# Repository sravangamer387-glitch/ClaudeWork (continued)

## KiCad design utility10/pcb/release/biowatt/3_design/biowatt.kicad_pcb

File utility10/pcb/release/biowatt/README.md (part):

# BioWatt MFC energy harvester (BQ25570) (rev A)

BioWatt microbial-fuel-cell energy harvester (44 x 40 mm): TI BQ25570 boost charger with MPPT, buck output, VBAT_OK, megohm setting dividers; one protected Li-ion cell as storage.

**Status: engineering release, software-verified only (ERC on the netlist, KiCad DRC, netlist cross-check, SPICE where noted). Not yet built, not reviewed by a second engineer, not certified.**

## Specification
- Board 44 x 40 mm, 2 layers, 1.6 mm FR-4, 1 oz copper, rounded corners R2.0 mm, 2 x M2.5 mounting holes, 2 fiducials.
- Rules used: min track 0.2 mm (power 0.4 mm), min clearance 0.15 mm, via 0.6/0.3 mm, GND pour on both layers, 30 stitching vias.
- Finish: ENIG recommended (HASL lead-free acceptable); green mask, white silk; IPC class 2.
- 29 parts, 20 nets.

## Circuit description
- **Harvester:** BQ25570 (SLUSBH2G). VIN_DC from the fuel cell through L1 = 22 uH, CIN 4.7 uF; VOC_SAMP tied to GND = MPPT at 50 % of Voc (the maximum-power point of a source with a linear polarisation curve); VREF_SAMP 10 nF; EN tied to GND (enabled); VOUT_EN tied to VSTOR; NC pins tied to the PowerPAD.
- **Settings (equations from the datasheet, VBIAS 1.21 V):** VBAT_OV 3.95 V (ROV1 5.6 M, ROV2 5.6 M + 1 M); VBAT_OK 3.35 V falling and 3.63 V rising (ROK1 4.3 M, ROK2 5.6 M + 1 M + 1 M, ROK3 1 M); VOUT 3.35 V (ROUT1 4.3 M, ROUT2 5.6 M + 1 M + 1 M). Dividers go from VRDIV to GND.
- **Output:** buck L2 = 10 uH, COUT 22 uF; header with VOUT, GND and the VBAT_OK flag for the sensor tag. Storage: a protected single Li-ion/LiPo cell on VBAT (22 uF) with CSTOR 4.7 uF + CBYP 0.1 uF at VSTOR.

## Power
Harvester quiescent about 0.5 uA (datasheet); output limited by what the fuel cell delivers (see biowatt/docs/budget.md).

## Verification
| Check | Result |
|---|---|
| Electrical rule check on the netlist (own ERC: unconnected pins, single-pin nets, output conflicts, unpowered supplies, symbol/footprint pin match) | 0 errors, 0 warnings |
| KiCad DRC | 0 errors, 0 warnings; unconnected pads: 0 |
| Schematic netlist equals PCB netlist | yes |
| Router failures | 0 |
| 3D STEP export | yes |
| Independent Gerber parse (gerbonara): layers parsed, outline size equals the design | 9 layers, outline [44.1, 40.1] mm, match |

Enclosure (prototype shell for 3D printing): outer 49.2 x 45.2 x 15.6 mm, collision/opening check: pass

## Bill of materials
| Ref | Value | Footprint | Manufacturer part | LCSC # | LCSC status |
|---|---|---|---|---|---|
| U1 | BQ25570RGRR | QFN-20-1EP_3.5x3.5mm_P0.5mm_EP2x2mm | BQ25570RGRR | C506250 | verified |
| J1 | MFC in (+ / -) | JST_PH_B2B-PH-K_1x02_P2.00mm_Vertical | JST B2B-PH-K-S | C131337 | verified |
| J2 | Storage cell (+ / -), protected | JST_PH_B2B-PH-K_1x02_P2.00mm_Vertical | JST B2B-PH-K-S | C131337 | verified |
| J3 | Tag out (VOUT, GND, VBAT_OK) | JST_PH_B3B-PH-K_1x03_P2.00mm_Vertical | JST B3B-PH-K-S | C131339 | verified |
| L1 | 22u | L_Coilcraft_LPS4018 | Coilcraft LPS4018-223MRC | C5278935 | verified |
| L2 | 10u | L_Changjiang_FNR3015S | ZE ZENR3015T100M | C42427989 | verified |
| C1 | 4.7u | C_0603_1608Metric | Samsung CL10A475KP8NNNC X5R 10V | C1705 | verified |
| C2 | 100n | C_0603_1608Metric | Samsung CL10B104KB8NNNC 0603 100nF X7R 50V | C1591 | verified |
| C3 | 4.7u | C_0603_1608Metric | Samsung CL10A475KP8NNNC X5R 10V | C1705 | verified |
| C4 | 22u/10V | C_0805_2012Metric | Samsung CL21A226MPQNNNE | C29277 | verified |
| C5 | 22u/10V | C_0805_2012Metric | Samsung CL21A226MPQNNNE | C29277 | verified |
| C6 | 10n | C_0603_1608Metric | Samsung CL10B103KB8NNNC 0603 10nF X7R 50V | C1589 | verified |
| R3 | 5.6M | R_0603_1608Metric | FOJAN FRC0603F5604TS | C2933237 | verified |
| R2 | 1M | R_0603_1608Metric | UNI-ROYAL 0603WAF1004T5E | C22935 | verified |
| R1 | 5.6M | R_0603_1608Metric | FOJAN FRC0603F5604TS | C2933237 | verified |
| R4 | 4.3M | R_0603_1608Metric | FH RS-03L4304FT | C136595 | verified |
| R5 | 5.6M | R_0603_1608Metric | FOJAN FRC0603F5604TS | C2933237 | verified |
| R6 | 1M | R_0603_1608Metric | UNI-ROYAL 0603WAF1004T5E | C22935 | verified |
| R7 | 1M | R_0603_1608Metric | UNI-ROYAL 0603WAF1004T5E | C22935 | verified |
| R8 | 1M | R_0603_1608Metric | UNI-ROYAL 0603WAF1004T5E | C22935 | verified |
| R9 | 1M | R_0603_1608Metric | UNI-ROYAL 0603WAF1004T5E | C22935 | verified |
| R10 | 4.3M | R_0603_1608Metric | FH RS-03L4304FT | C136595 | verified |
| R11 | 5.6M | R_0603_1608Metric | FOJAN FRC0603F5604TS | C2933237 | verified |
| R12 | 1M | R_0603_1608Metric | UNI-ROYAL 0603WAF1004T5E | C22935 | verified |
| R13 | 1M | R_0603_1608Metric | UNI-ROYAL 0603WAF1004T5E | C22935 | verified |
| TP1 | TP | TestPoint_Pad_D1.5mm |  |  |  |
| TP2 | TP | TestPoint_Pad_D1.5mm |  |  |  |
| TP3 | TP | TestPoint_Pad_D1.5mm |  |  |  |
| TP4 | TP | TestPoint_Pad_D1.5mm |  |  |  |

`verified` = LCSC number confirmed by web search on 2026-10-31/11-01; `memory` = from my recollection, **check on lcsc.com before ordering**; empty = no number chosen (through-hole connectors, switches, buzzer, test points: hand-assembled or chosen by the buyer). `*_JLC_BOM.csv` / `*_JLC_CPL.csv` list only the parts with an LCSC number; JLCPCB rotation corrections (CPL) must be checked in their viewer.

## Assembly notes
- Reflow (JLCPCB SMT): all SMD parts with an LCSC number. Hand-solder: JST connectors, pin headers, buzzer, switches, test points as listed in the BOM. Fiducials and mounting holes are in the Gerbers.
- Polarity: LED cathode toward GND (silk marks), electrolytic none, diode D2 cathode to +V, Q2 orientation as footprint (SOT-23 pin 1 = gate).
- Programming: ISP header J2 (pin 1 = MISO, square pad). Flash the matching image from `utility10/firmware/release/`: Seeti Counter `4MHz/seeti_prod.hex` (production firmware: timer-triggered 16 kS/s ADC, scan mode to find the real whistle frequency, battery check), Rain Alert `8MHz/rain_alert.hex`, Bijli Meter Reader `8MHz/bijli_meter.hex` (demo-grade firmware, to be hardened).

## Bring-up and test
1. With no cell and no source: nothing to measure; check no shorts VSTOR-GND, VOUT-GND.
2. Fit the protected cell: VSTOR follows the cell, VBAT_OK goes high above about 3.63 V.
3. Feed 0.6-1.0 V from a bench supply through 1 kohm: VSTOR rises (cold start needs VIN of at least 0.6 V).
4. Connect the fuel cell, measure VIN_DC under load: it should settle near half of the open-circuit voltage.
5. Measure VOUT = 3.35 V +-3 %.

## Files
`1_fabrication/` Gerber + drill zip (upload to JLCPCB/any fab), fab notes, copper plot
`2_assembly/` JLC BOM + CPL (SMD parts JLC assembles), full BOM with LCSC numbers for every part, pick-and-place, assembly drawing
`3_design/` KiCad 7 project (pcb, schematic, libs), netlist, STEP model, schematic PDF, renders
`4_enclosure/` printable base and lid STL
`5_verification/` DRC, ERC, verification and readiness reports

## Known limits and review checklist
- Layout was produced by a custom router and software placement; a human layout review (analog routing, ground returns, creepage, connector mechanics, silkscreen) is still required.
- Not verified: EMC, ESD (apart from TVS parts where fitted), thermal, real component tolerances, supplier stock/price, assembly house design-for-manufacture check (run JLCPCB's DFM check on the Gerbers).
- Firmware thresholds are placeholders to be calibrated on prototypes.

## Manufacturing readiness (automatic check)

| Check | Result |
|---|---|
| gerber layers and drill present | PASS |
| drc errors 0 | PASS |
| unconnected 0 | PASS |
| netlist matches schematic | PASS |
| erc errors 0 | PASS |
| independent gerber check clean | PASS |
| every part has lcsc number | PASS |
| every lcsc number verified | PASS |
| cpl rows equal jlc bom parts | PASS |
| step model | PASS |
| KiCad DRC warnings | 0 |
| **Order ready** | **YES** |

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
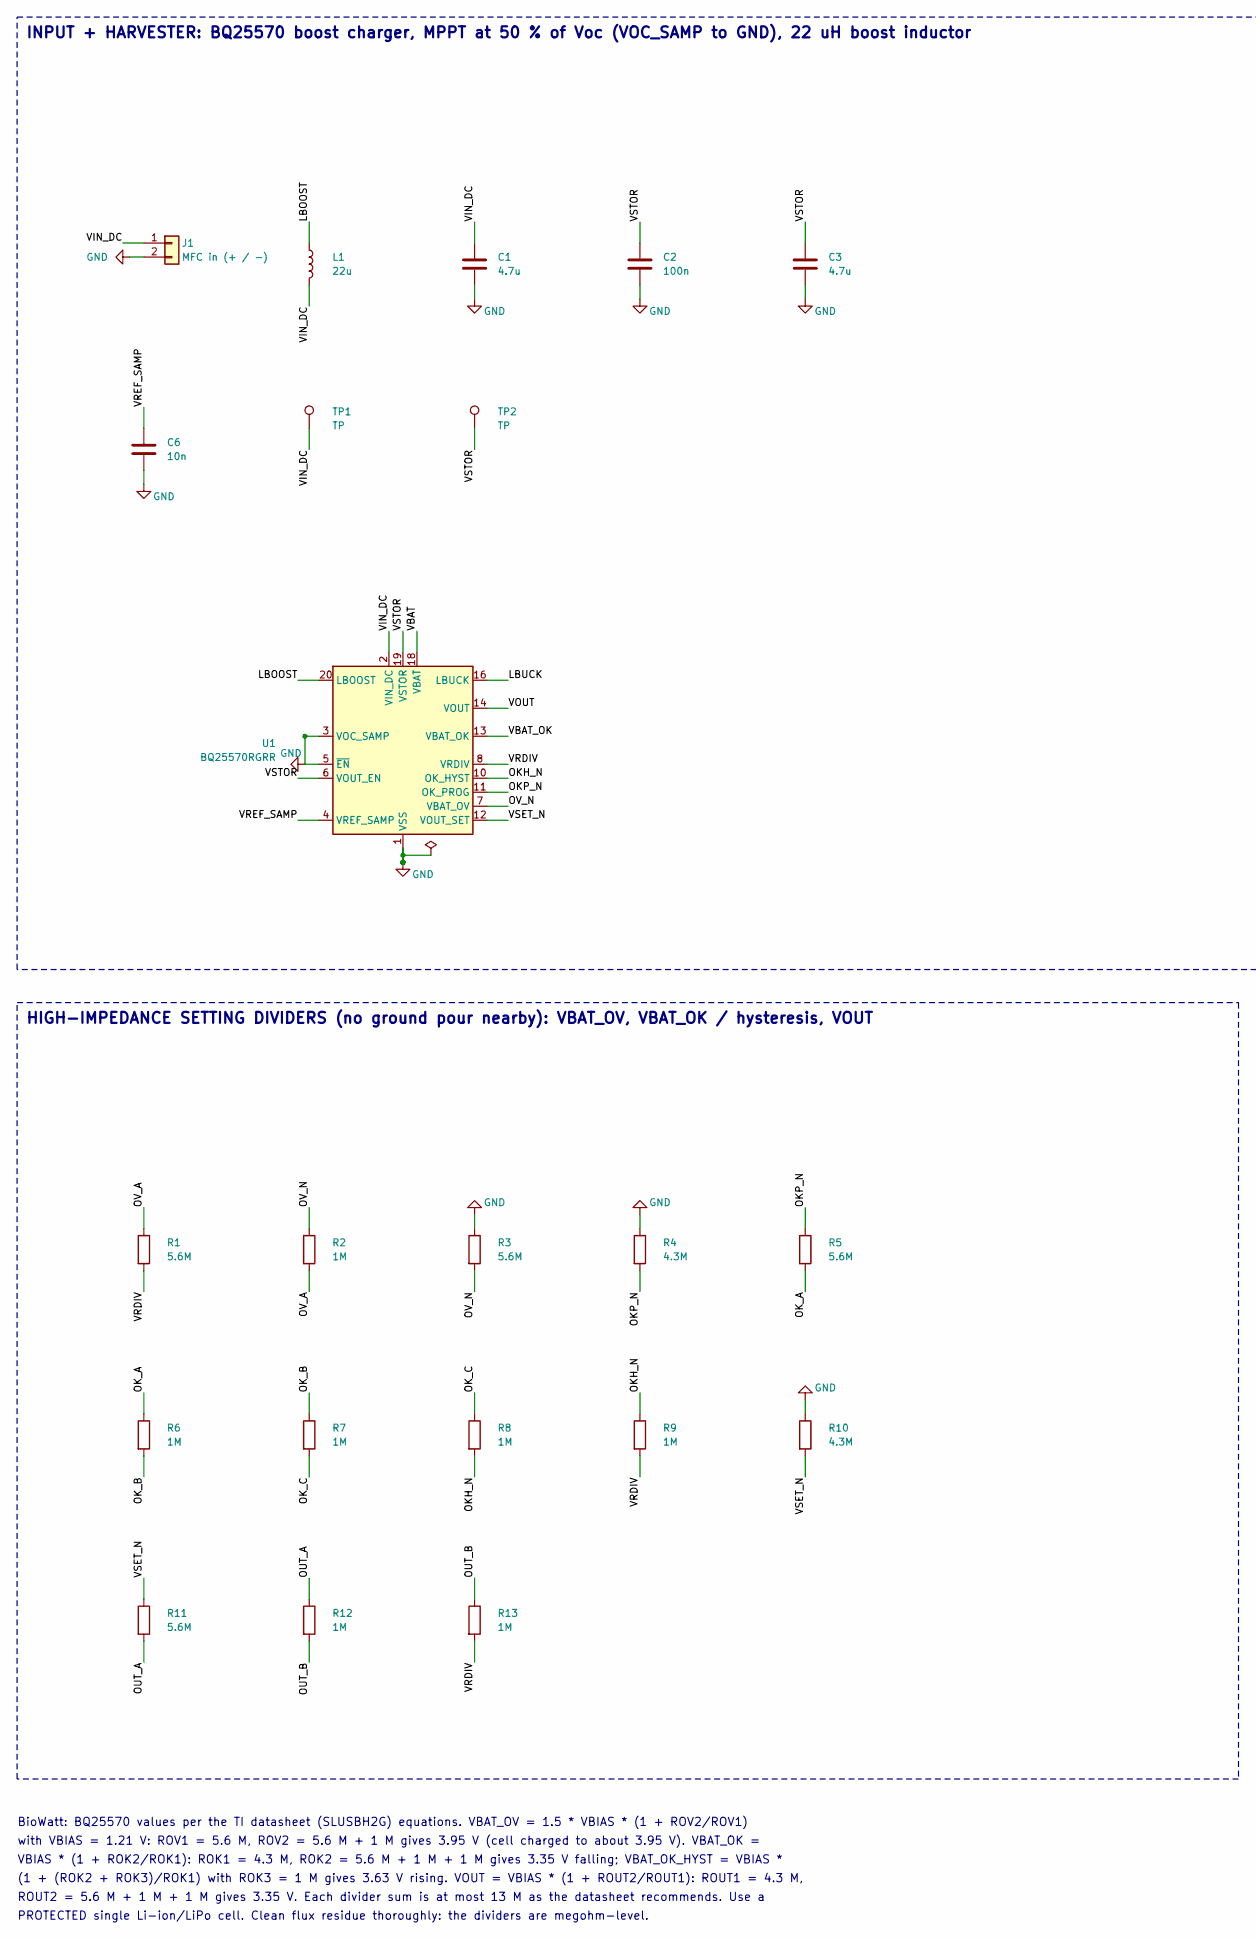
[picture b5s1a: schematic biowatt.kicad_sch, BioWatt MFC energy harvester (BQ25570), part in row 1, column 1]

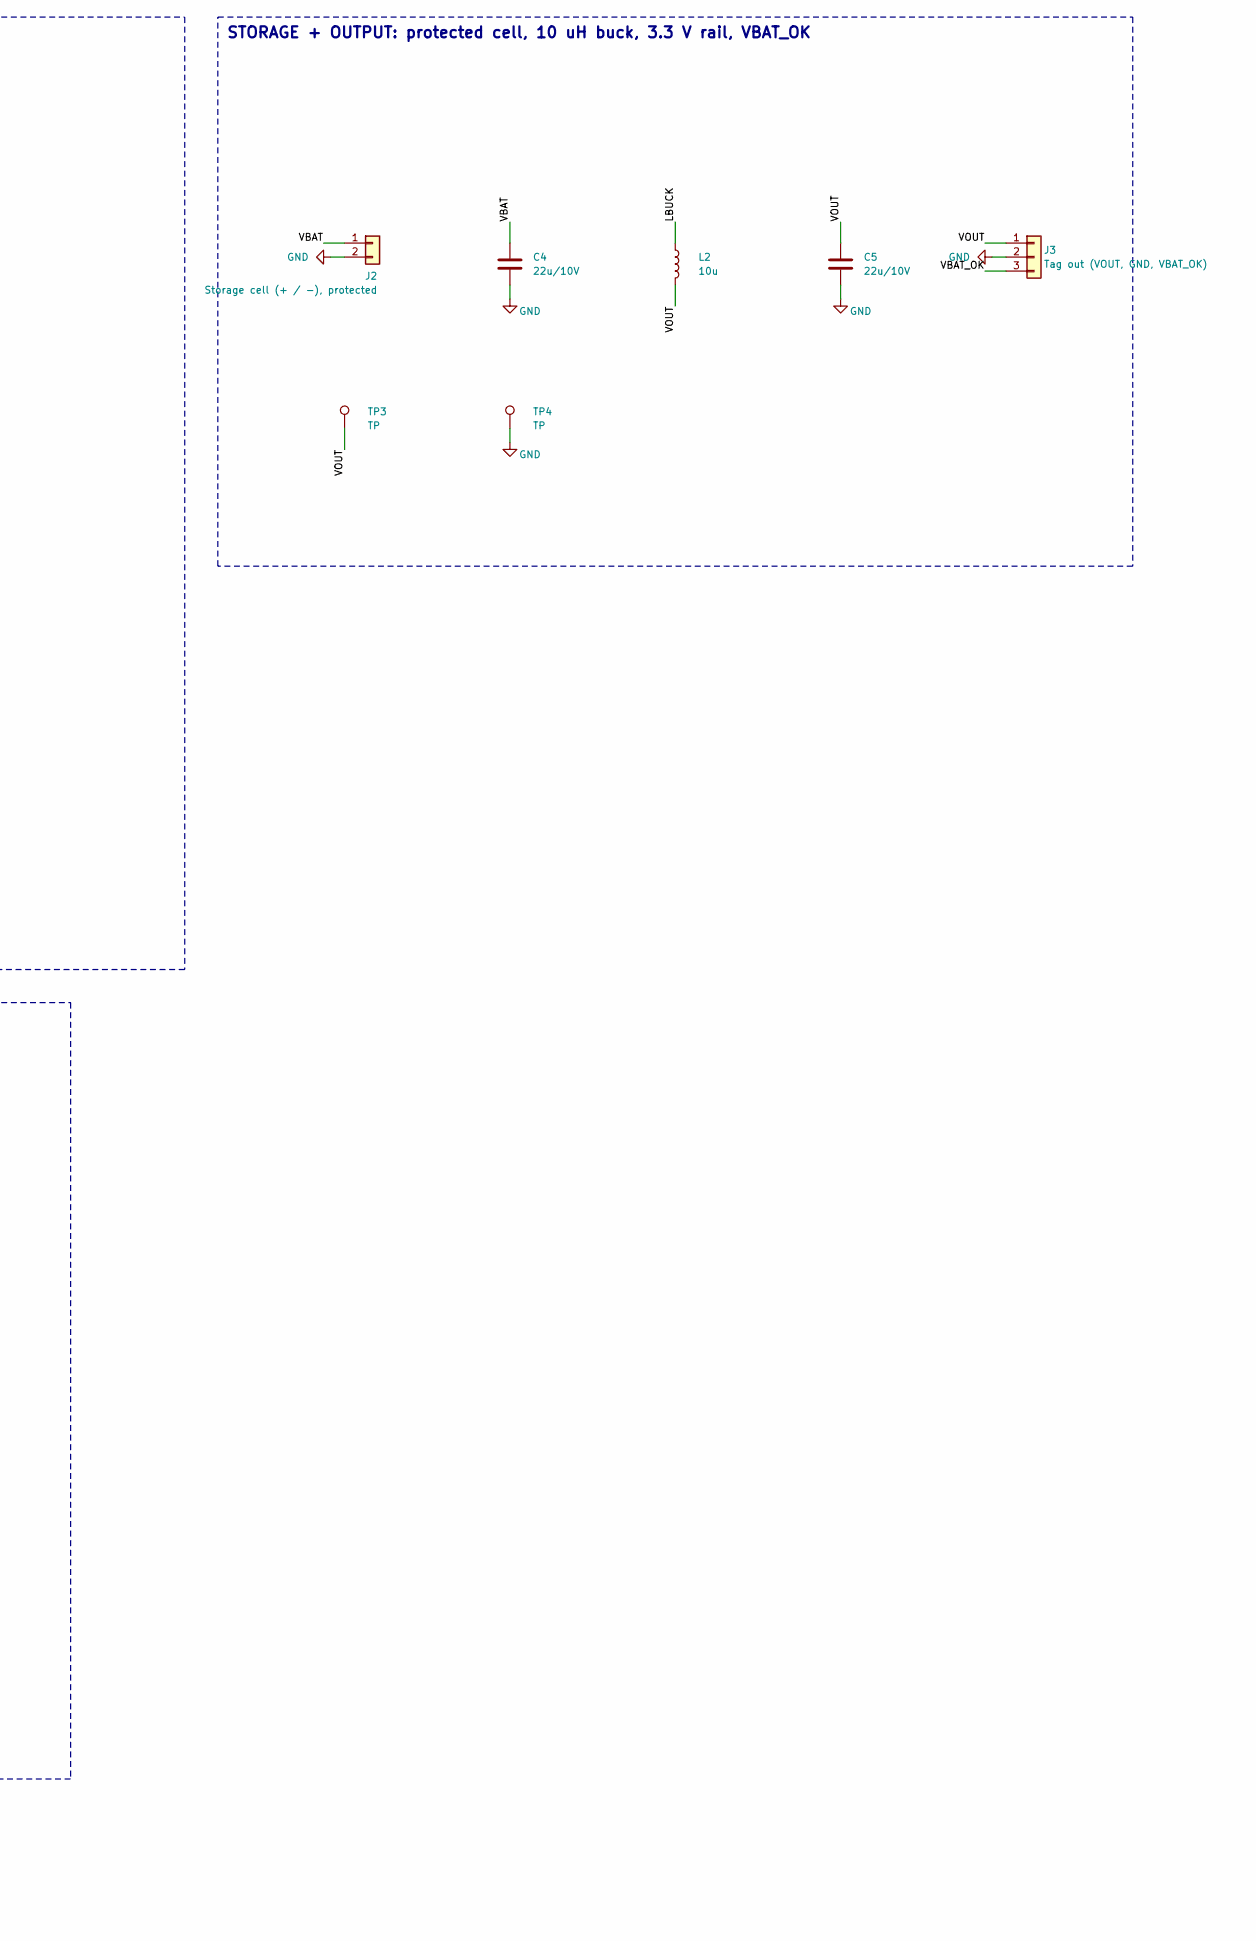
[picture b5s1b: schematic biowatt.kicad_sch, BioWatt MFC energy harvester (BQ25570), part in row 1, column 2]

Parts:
C1, C3: 4.7u; C_0603_1608Metric
C2: 100n; C_0603_1608Metric
C4, C5: 22u/10V; C_0805_2012Metric
C6: 10n; C_0603_1608Metric
J1: MFC in (+ / -); JST_PH_B2B-PH-K_1x02_P2.00mm_Vertical
J2: Storage cell (+ / -), protected; JST_PH_B2B-PH-K_1x02_P2.00mm_Vertical
J3: Tag out (VOUT, GND, VBAT_OK); JST_PH_B3B-PH-K_1x03_P2.00mm_Vertical
L1: 22u; L_Coilcraft_LPS4018
L2: 10u; L_Changjiang_FNR3015S
R1, R3, R5, R11: 5.6M; R_0603_1608Metric
R2, R6, R7, R8, R9, R12, R13: 1M; R_0603_1608Metric
R4, R10: 4.3M; R_0603_1608Metric
TP1, TP2, TP3, TP4: TP; TestPoint_Pad_D1.5mm
U1: BQ25570RGRR; QFN-20-1EP_3.5x3.5mm_P0.5mm_EP2x2mm

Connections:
GND: C1.2, C2.2, C3.2, C4.2, C5.2, C6.2, J1.2, J2.2, J3.2, R3.1, R4.1, R10.1, TP4.1, U1.1 (VSS), U1.3 (VOC_SAMP), U1.5 (~EN), U1.9 (VSS), U1.15 (VSS), U1.17 (VSS), U1.21 (VSS)
LBOOST: L1.1, U1.20 (LBOOST)
LBUCK: L2.1, U1.16 (LBUCK)
OKH_N: R8.2, R9.1, U1.10 (OK_HYST)
OKP_N: R4.2, R5.1, U1.11 (OK_PROG)
OK_A: R5.2, R6.1
OK_B: R6.2, R7.1
OK_C: R7.2, R8.1
OUT_A: R11.2, R12.1
OUT_B: R12.2, R13.1
OV_A: R1.1, R2.2
OV_N: R2.1, R3.2, U1.7 (VBAT_OV)
VBAT: C4.1, J2.1, U1.18 (VBAT)
VBAT_OK: J3.3, U1.13 (VBAT_OK)
VIN_DC: C1.1, J1.1, L1.2, TP1.1, U1.2 (VIN_DC)
VOUT: C5.1, J3.1, L2.2, TP3.1, U1.14 (VOUT)
VRDIV: R1.2, R9.2, R13.2, U1.8 (VRDIV)
VREF_SAMP: C6.1, U1.4 (VREF_SAMP)
VSET_N: R10.2, R11.1, U1.12 (VOUT_SET)
VSTOR: C2.1, C3.1, TP2.1, U1.6 (VOUT_EN), U1.19 (VSTOR)

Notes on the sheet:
INPUT + HARVESTER: BQ25570 boost charger, MPPT at 50 % of Voc (VOC_SAMP to GND), 22 uH boost inductor
STORAGE + OUTPUT: protected cell, 10 uH buck, 3.3 V rail, VBAT_OK
HIGH-IMPEDANCE SETTING DIVIDERS (no ground pour nearby): VBAT_OV, VBAT_OK / hysteresis, VOUT
BioWatt: BQ25570 values per the TI datasheet (SLUSBH2G) equations. VBAT_OV = 1.5 * VBIAS * (1 + ROV2/ROV1)
with VBIAS = 1.21 V: ROV1 = 5.6 M, ROV2 = 5.6 M + 1 M gives 3.95 V (cell charged to about 3.95 V). VBAT_OK =
VBIAS * (1 + ROK2/ROK1): ROK1 = 4.3 M, ROK2 = 5.6 M + 1 M + 1 M gives 3.35 V falling; VBAT_OK_HYST = VBIAS *
(1 + (ROK2 + ROK3)/ROK1) with ROK3 = 1 M gives 3.63 V rising. VOUT = VBIAS * (1 + ROUT2/ROUT1): ROUT1 = 4.3 M,
ROUT2 = 5.6 M + 1 M + 1 M gives 3.35 V. Each divider sum is at most 13 M as the datasheet recommends. Use a
PROTECTED single Li-ion/LiPo cell. Clean flux residue thoroughly: the dividers are megohm-level.

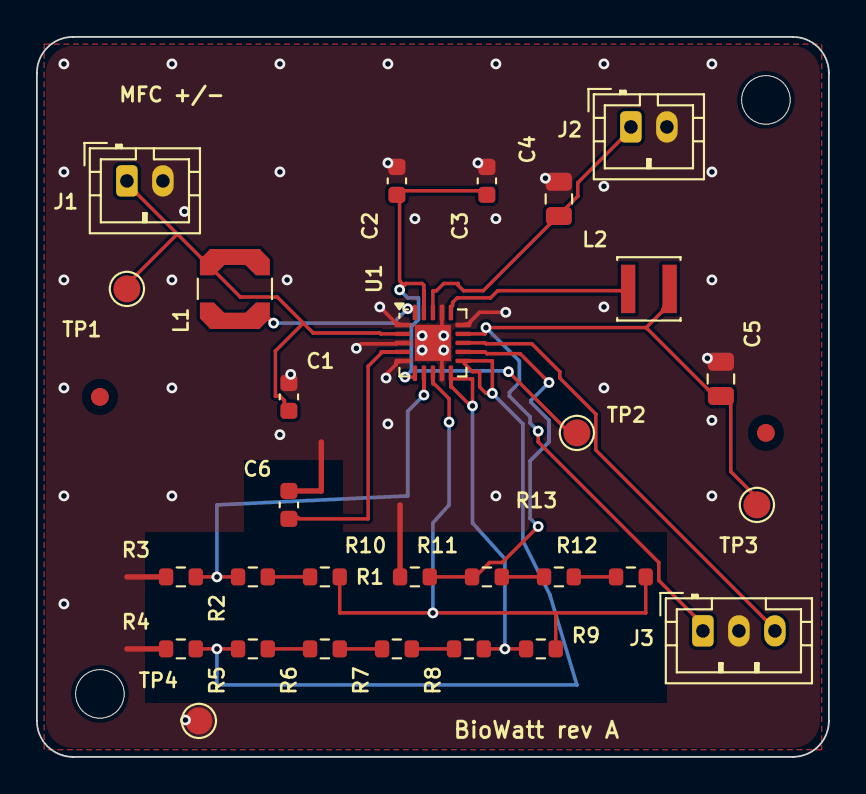
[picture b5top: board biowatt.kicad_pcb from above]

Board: 2 copper layers, 44.0 x 40.0 mm, 33 parts (0 on the bottom side), 20 nets.

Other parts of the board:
FID1, FID2: Fiducial; Fiducial_1mm_Mask2mm
H1, H2: M2.5; MountingHole_2.7mm_M2.5

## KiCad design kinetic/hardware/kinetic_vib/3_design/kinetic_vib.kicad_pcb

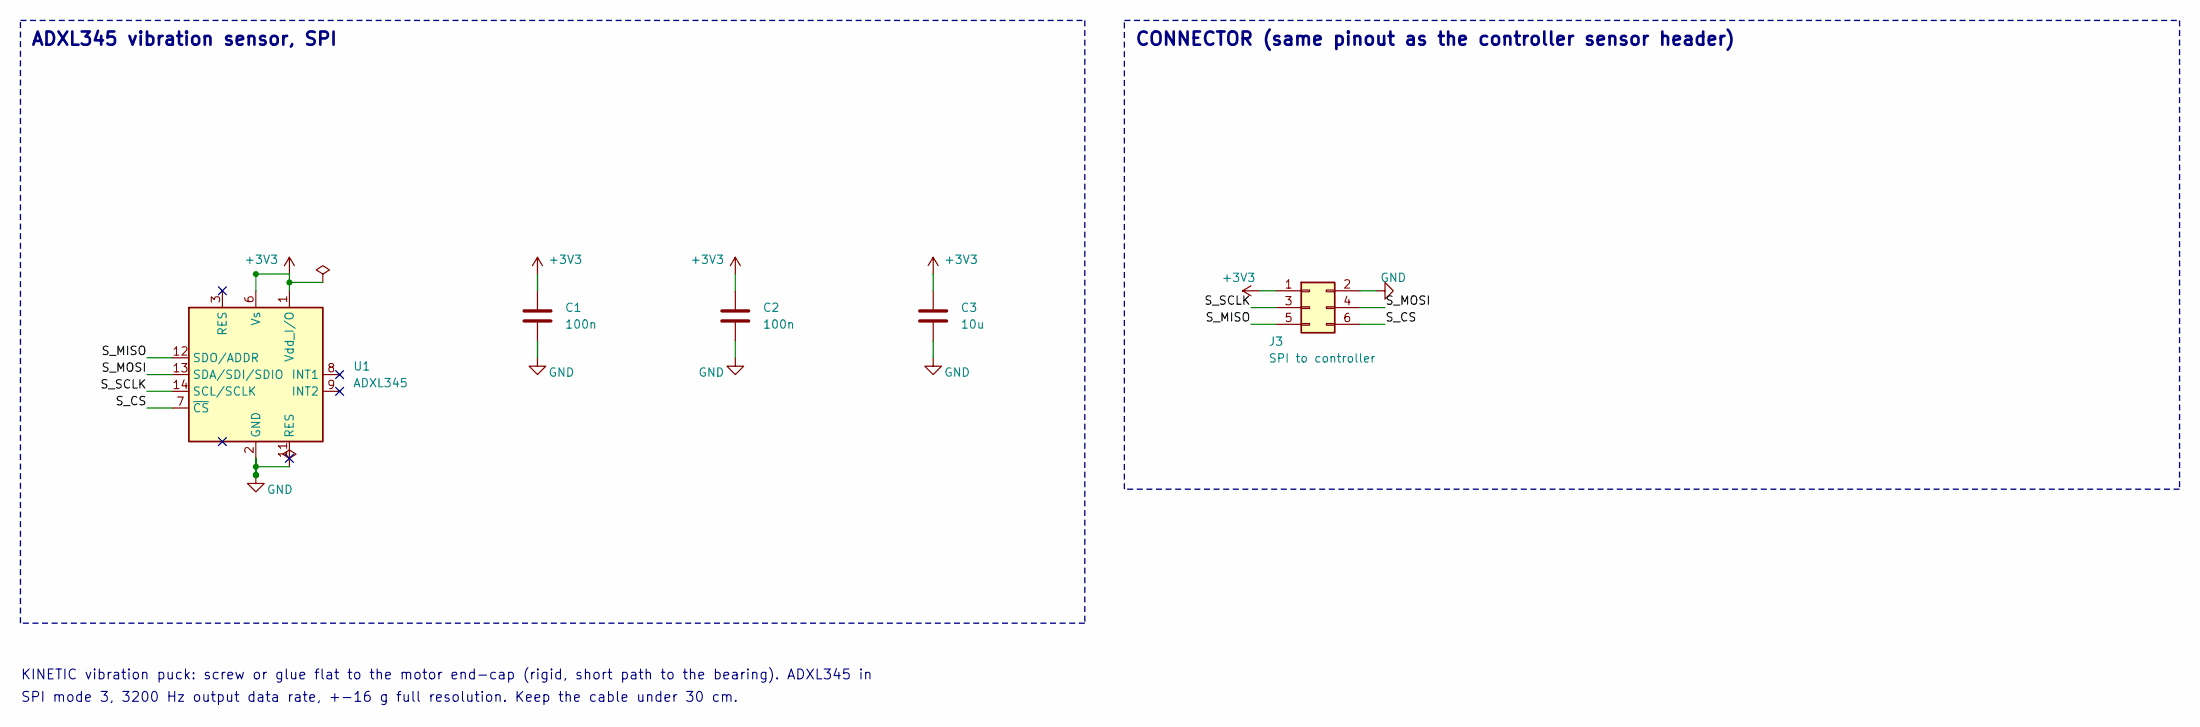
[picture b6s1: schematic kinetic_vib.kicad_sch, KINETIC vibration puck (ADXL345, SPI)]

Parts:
C1, C2: 100n; C_0603_1608Metric
C3: 10u; C_0805_2012Metric
J3: SPI to controller; PinHeader_2x03_P2.54mm_Vertical
U1: ADXL345; LGA-14_3x5mm_P0.8mm_LayoutBorder1x6y

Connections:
+3V3: C1.1, C2.1, C3.1, J3.1, U1.1 (Vdd_I/O), U1.6 (Vs)
GND: C1.2, C2.2, C3.2, J3.2, U1.2 (GND), U1.4 (GND), U1.5 (GND)
S_CS: J3.6, U1.7 (~CS)
S_MISO: J3.5, U1.12 (SDO/ADDR)
S_MOSI: J3.4, U1.13 (SDA/SDI/SDIO)
S_SCLK: J3.3, U1.14 (SCL/SCLK)

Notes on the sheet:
ADXL345 vibration sensor, SPI
CONNECTOR (same pinout as the controller sensor header)
KINETIC vibration puck: screw or glue flat to the motor end-cap (rigid, short path to the bearing). ADXL345 in
SPI mode 3, 3200 Hz output data rate, +-16 g full resolution. Keep the cable under 30 cm.

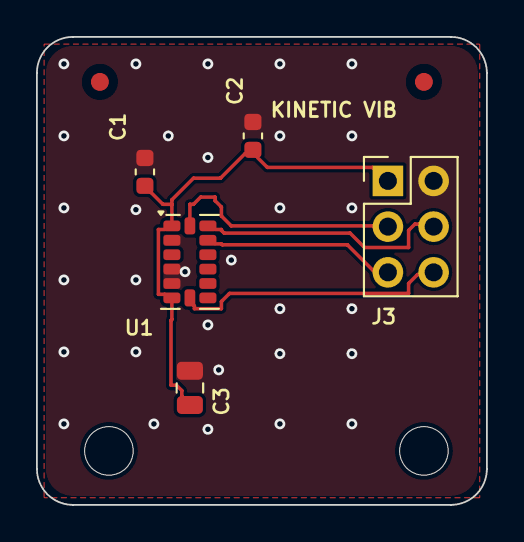
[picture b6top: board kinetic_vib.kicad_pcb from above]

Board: 2 copper layers, 25.0 x 26.0 mm, 9 parts (0 on the bottom side), 6 nets.

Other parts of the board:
FID1, FID2: Fiducial; Fiducial_1mm_Mask2mm
H1, H2: M2.5; MountingHole_2.7mm_M2.5

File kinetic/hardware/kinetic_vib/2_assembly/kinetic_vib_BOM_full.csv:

Ref,Value,Footprint,Manufacturer part,LCSC #,LCSC status,Assembly
U1,ADXL345,Package_LGA:LGA-14_3x5mm_P0.8mm_LayoutBorder1x6y,ADXL345BCCZ-RL7,C9667,verified,SMT (JLC)
C1,100n,Capacitor_SMD:C_0603_1608Metric,0603 100nF X7R,C14663,verified,SMT (JLC)
C2,100n,Capacitor_SMD:C_0603_1608Metric,0603 100nF X7R,C14663,verified,SMT (JLC)
C3,10u,Capacitor_SMD:C_0805_2012Metric,0805 10uF X5R,C15850,verified,SMT (JLC)
J3,SPI to controller,Connector_PinHeader_2.54mm:PinHeader_2x03_P2.54mm_Vertical,ZHOURI 2.54-2*3,C5116479,verified,hand/THT

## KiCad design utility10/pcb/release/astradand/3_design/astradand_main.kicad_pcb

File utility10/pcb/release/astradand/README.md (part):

# ASTRADAND gesture wand - main board (rev A)

ASTRADAND gesture wand main board (146 x 26 mm): ATmega328P at 8 MHz and 3.3 V, MPU-6050 6-axis IMU on I2C, six WS2812B-Mini pixels, differential piezo, haptic motor driver, trigger switch, 3xAAA power with reverse-polarity PMOS.

**Status: engineering release, software-verified only (ERC on the netlist, KiCad DRC, netlist cross-check, SPICE where noted). Not yet built, not reviewed by a second engineer, not certified.**

## Specification
- Board 146 x 26 mm, 2 layers, 1.6 mm FR-4, 1 oz copper, rounded corners R2.5 mm, 2 x M2.5 mounting holes, 2 fiducials.
- Rules used: min track 0.2 mm (power 0.4 mm), min clearance 0.15 mm, via 0.6/0.3 mm, GND pour on both layers, 182 stitching vias.
- Finish: ENIG recommended (HASL lead-free acceptable); green mask, white silk; IPC class 2.
- 49 parts, 33 nets.

## Circuit description
- **Motion:** MPU-6050 on I2C (4.7k pull-ups, SDA/SCL taken under the board on the bottom layer), wake-on-motion interrupt to the MCU; AD0/FSYNC/CLKIN tied to GND.
- **Light:** six WS2812B-Mini pixels in a chain, each with 100 nF; data from D10 through 330 ohm; the LED supply is switched high-side (AO3401A driven by MMBT3904) through an SS14 so the pixels draw nothing in sleep and their 5 V-class data is met at 3.3 V logic by running the strip from the battery rail.
- **Sound/haptic:** piezo driven antiphase from Timer1 (OC1A/OC1B); vibration motor through an NPN with flyback diode.
- **Power:** 3xAAA, slide switch, AO3401A reverse-polarity PMOS, AP2112K 3.3 V LDO, battery divider to ADC for the low-battery warning.

## Power
Sleep with IMU wake-on-motion: target tens of microamps (not measured). Active casting with LEDs lit is dominated by the six pixels (tens of mA).

## Verification
| Check | Result |
|---|---|
| Electrical rule check on the netlist (own ERC: unconnected pins, single-pin nets, output conflicts, unpowered supplies, symbol/footprint pin match) | 0 errors, 0 warnings |
| KiCad DRC | 0 errors, 0 warnings; unconnected pads: 0 |
| Schematic netlist equals PCB netlist | yes |
| Router failures | 0 |
| 3D STEP export | yes |
| Independent Gerber parse (gerbonara): layers parsed, outline size equals the design | 9 layers, outline [146.1, 26.1] mm, match |

Enclosure (prototype shell for 3D printing): outer 151.2 x 31.2 x 19.6 mm, collision/opening check: pass

## Bill of materials
| Ref | Value | Footprint | Manufacturer part | LCSC # | LCSC status |
|---|---|---|---|---|---|
| U1 | ATmega328P-AU | TQFP-32_7x7mm_P0.8mm | ATMEGA328P-AU | C14877 | verified |
| C1 | 100n | C_0603_1608Metric | Samsung CL10B104KB8NNNC 0603 100nF X7R 50V | C1591 | verified |
| C2 | 100n | C_0603_1608Metric | Samsung CL10B104KB8NNNC 0603 100nF X7R 50V | C1591 | verified |
| C3 | 100n | C_0603_1608Metric | Samsung CL10B104KB8NNNC 0603 100nF X7R 50V | C1591 | verified |
| R7 | 10k | R_0603_1608Metric | 0603 10k 1% | C25804 | verified |
| J2 | ISP | PinHeader_2x03_P2.54mm_Vertical | HCTL PZ254-2-03-Z-8.5 (ZHOURI C5116479 had only 340 in stock) | C2894964 | verified |
| J1 | BATT 3xAAA | JST_PH_B2B-PH-K_1x02_P2.00mm_Vertical | JST B2B-PH-K-S(LF)(SN) | C131337 | verified |
| SW1 | Power | SW_SPDT_PCM12 | C&K PCM12SMTR | C221841 | verified |
| Q2 | AO3401A | SOT-23 | AO3401A | C15127 | verified |
| C4 | 10u | C_0805_2012Metric | 0805 10uF X5R | C15850 | verified |
| D11 | WS2812B-Mini | LED_WS2812B-Mini_PLCC4_3.5x3.5mm | OPSCO SK6812MINI-B-012 SMD3535-4P, same pin order and 800 kHz protocol as the WS2812B-Mini (Worldsemi parts were sold out) | C5183448 | verified |
| C20 | 100n | C_0603_1608Metric | Samsung CL10B104KB8NNNC 0603 100nF X7R 50V | C1591 | verified |
| D12 | WS2812B-Mini | LED_WS2812B-Mini_PLCC4_3.5x3.5mm | OPSCO SK6812MINI-B-012 SMD3535-4P, same pin order and 800 kHz protocol as the WS2812B-Mini (Worldsemi parts were sold out) | C5183448 | verified |
| C21 | 100n | C_0603_1608Metric | Samsung CL10B104KB8NNNC 0603 100nF X7R 50V | C1591 | verified |
| D13 | WS2812B-Mini | LED_WS2812B-Mini_PLCC4_3.5x3.5mm | OPSCO SK6812MINI-B-012 SMD3535-4P, same pin order and 800 kHz protocol as the WS2812B-Mini (Worldsemi parts were sold out) | C5183448 | verified |
| C22 | 100n | C_0603_1608Metric | Samsung CL10B104KB8NNNC 0603 100nF X7R 50V | C1591 | verified |
| D14 | WS2812B-Mini | LED_WS2812B-Mini_PLCC4_3.5x3.5mm | OPSCO SK6812MINI-B-012 SMD3535-4P, same pin order and 800 kHz protocol as the WS2812B-Mini (Worldsemi parts were sold out) | C5183448 | verified |
| C23 | 100n | C_0603_1608Metric | Samsung CL10B104KB8NNNC 0603 100nF X7R 50V | C1591 | verified |
| D15 | WS2812B-Mini | LED_WS2812B-Mini_PLCC4_3.5x3.5mm | OPSCO SK6812MINI-B-012 SMD3535-4P, same pin order and 800 kHz protocol as the WS2812B-Mini (Worldsemi parts were sold out) | C5183448 | verified |
| C24 | 100n | C_0603_1608Metric | Samsung CL10B104KB8NNNC 0603 100nF X7R 50V | C1591 | verified |
| D16 | WS2812B-Mini | LED_WS2812B-Mini_PLCC4_3.5x3.5mm | OPSCO SK6812MINI-B-012 SMD3535-4P, same pin order and 800 kHz protocol as the WS2812B-Mini (Worldsemi parts were sold out) | C5183448 | verified |
| C25 | 100n | C_0603_1608Metric | Samsung CL10B104KB8NNNC 0603 100nF X7R 50V | C1591 | verified |
| U2 | MPU-6050 | InvenSense_QFN-24_4x4mm_P0.5mm | MPU-6050 | C24112 | verified |
| C10 | 100n | C_0603_1608Metric | Samsung CL10B104KB8NNNC 0603 100nF X7R 50V | C1591 | verified |
| C11 | 2.2n | C_0603_1608Metric | Samsung CL10B222KB8NNNC X7R | C16033 | verified |
| C12 | 100n | C_0603_1608Metric | Samsung CL10B104KB8NNNC 0603 100nF X7R 50V | C1591 | verified |
| C13 | 100n | C_0603_1608Metric | Samsung CL10B104KB8NNNC 0603 100nF X7R 50V | C1591 | verified |
| R20 | 4.7k | R_0603_1608Metric | 0603 4.7k 1% | C23162 | verified |
| R21 | 4.7k | R_0603_1608Metric | 0603 4.7k 1% | C23162 | verified |
| U3 | AP2112K-3.3 | SOT-23-5 | Diodes AP2112K-3.3TRG1 (from the LCSC datasheet link) | C51118 | verified |
| C5 | 1u | C_0603_1608Metric | 0603 1uF X7R | C15849 | verified |
| C6 | 1u | C_0603_1608Metric | 0603 1uF X7R | C15849 | verified |
| D20 | SS14 | D_SMA | Starsea SS14 SMA | C84343 | verified |
| Q3 | AO3401A | SOT-23 | AO3401A | C15127 | verified |
| Q4 | MMBT3904 | SOT-23 | MMBT3904 | C20526 | verified |
| R33 | 100k | R_0603_1608Metric | 0603 100k 1% | C25803 | verified |
| R34 | 1k | R_0603_1608Metric | 0603 1k 1% | C21190 | verified |
| C7 | 10u | C_0805_2012Metric | 0805 10uF X5R | C15850 | verified |
| R30 | 330 | R_0603_1608Metric | UNI-ROYAL 0603WAF3300T5E | C23138 | verified |
| R31 | 330k | R_0603_1608Metric | UNI-ROYAL 0603WAF3303T5E | C23137 | verified |
| R32 | 100k | R_0603_1608Metric | 0603 100k 1% | C25803 | verified |
| BZ1 | PKLCS1212E4001 | Buzzer_Murata_PKLCS1212E | PKLCS1212E4001-R1 | C113159 | verified |
| SW2 | Cast trigger | SW_SPST_B3U-1000P | Omron B3U-1000P | C231329 | verified |
| Q1 | MMBT3904 | SOT-23 | MMBT3904 | C20526 | verified |
| D2 | 1N4148WS | D_SOD-323 | 1N4148WS | C2128 | verified |
| R6 | 1k | R_0603_1608Metric | 0603 1k 1% | C21190 | verified |
| J4 | Haptic motor | JST_PH_B2B-PH-K_1x02_P2.00mm_Vertical | JST B2B-PH-K-S(LF)(SN) | C131337 | verified |
| TP1 | TP | TestPoint_Pad_D1.5mm |  |  |  |
| TP2 | TP | TestPoint_Pad_D1.5mm |  |  |  |

`verified` = LCSC number confirmed by web search on 2026-10-31/11-01; `memory` = from my recollection, **check on lcsc.com before ordering**; empty = no number chosen (through-hole connectors, switches, buzzer, test points: hand-assembled or chosen by the buyer). `*_JLC_BOM.csv` / `*_JLC_CPL.csv` list only the parts with an LCSC number; JLCPCB rotation corrections (CPL) must be checked in their viewer.

## Assembly notes
- Reflow (JLCPCB SMT): all SMD parts with an LCSC number. Hand-solder: JST connectors, pin headers, buzzer, switches, test points as listed in the BOM. Fiducials and mounting holes are in the Gerbers.
- Polarity: LED cathode toward GND (silk marks), electrolytic none, diode D2 cathode to +V, Q2 orientation as footprint (SOT-23 pin 1 = gate).
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
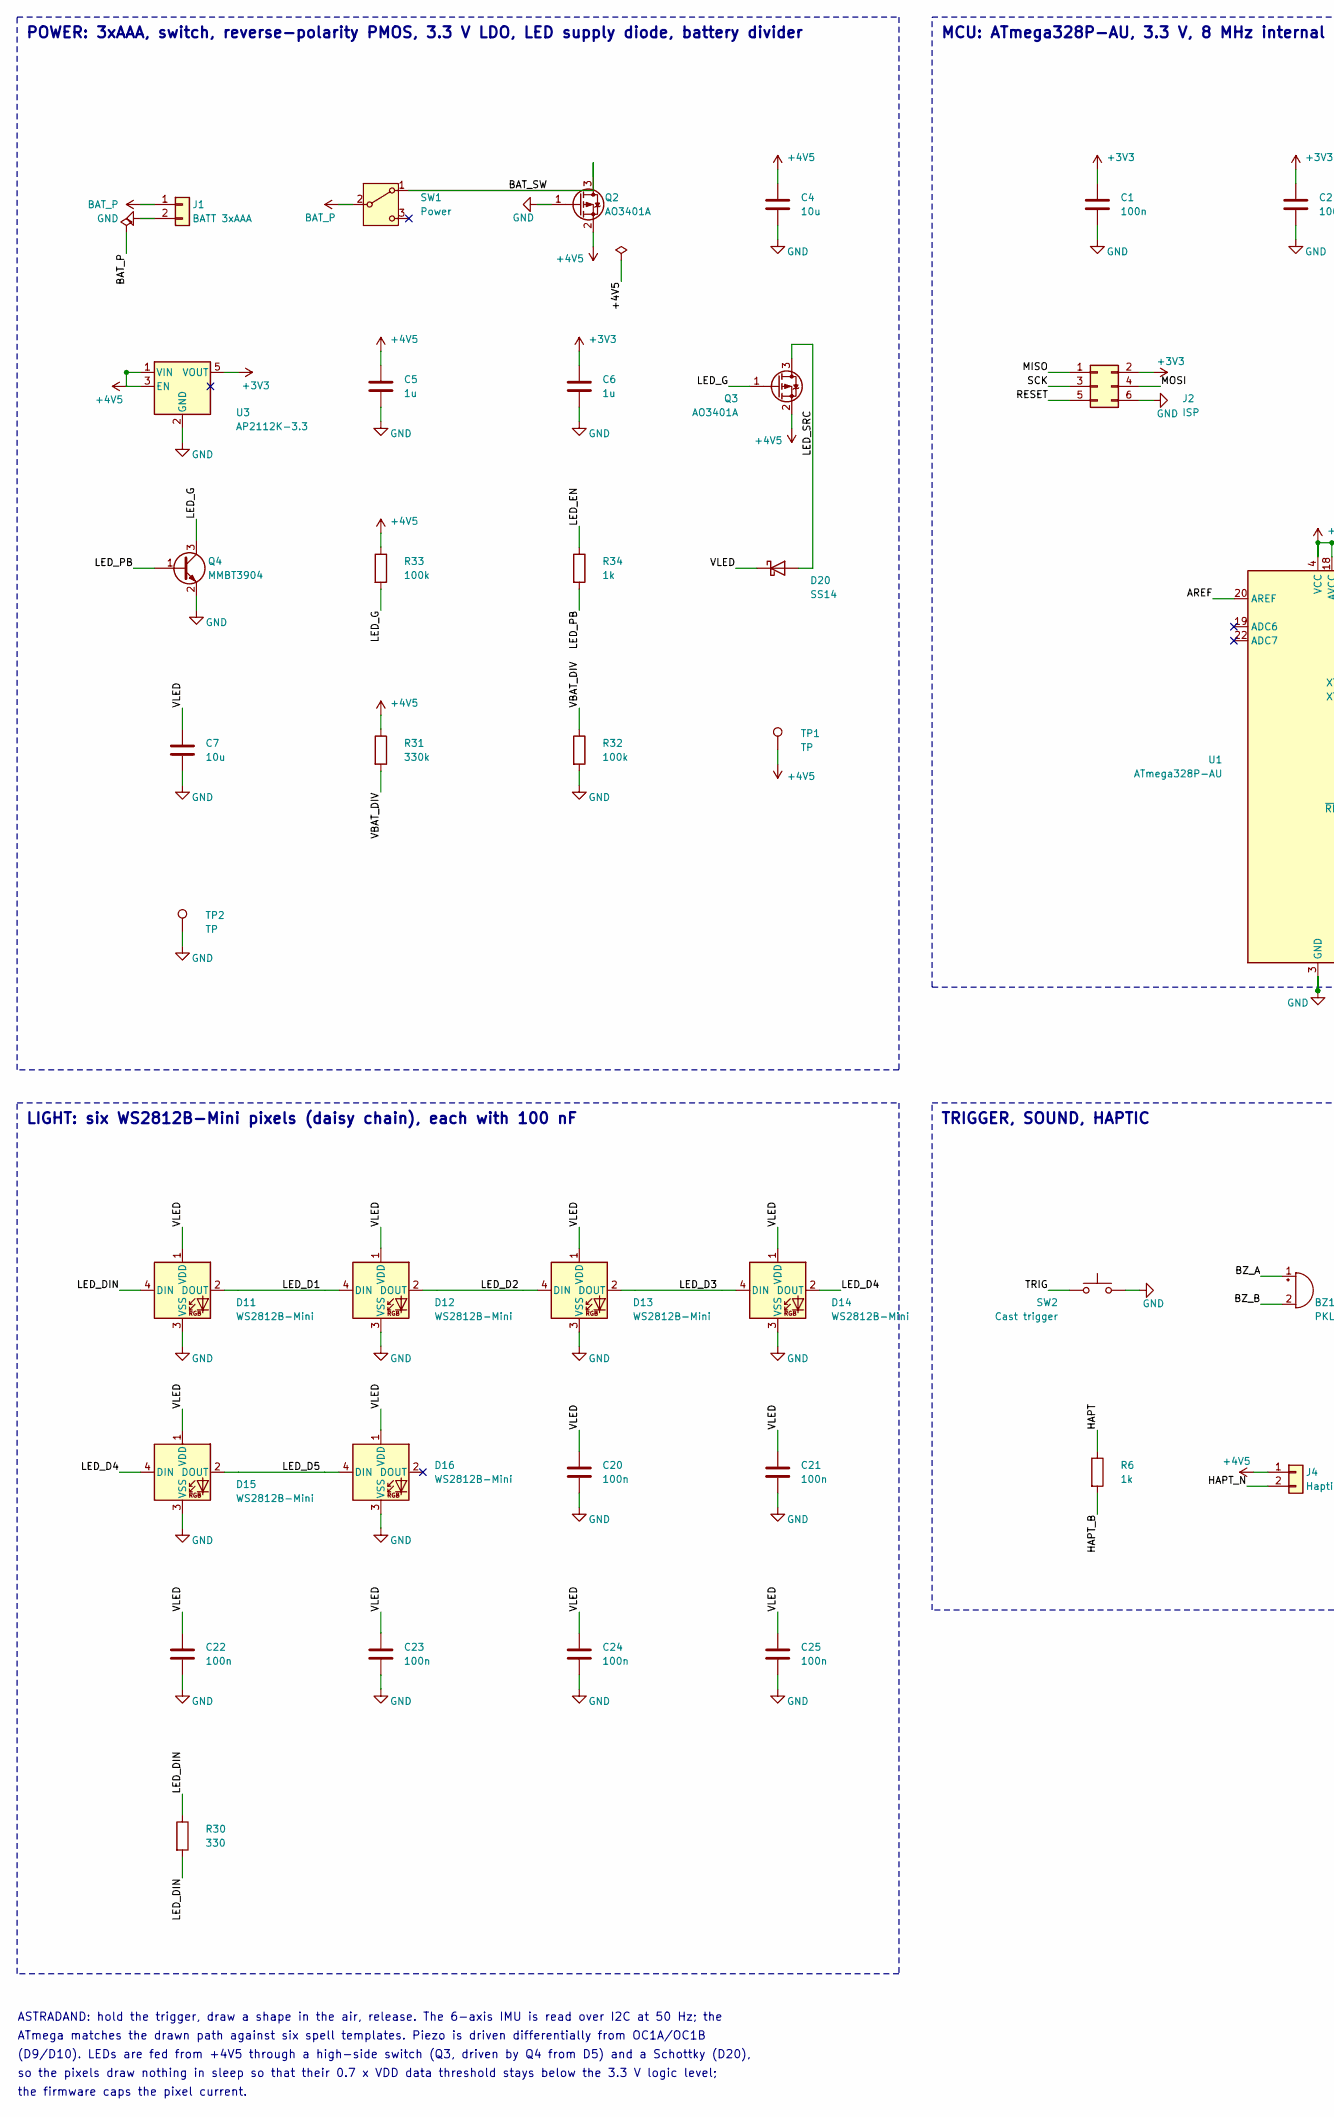
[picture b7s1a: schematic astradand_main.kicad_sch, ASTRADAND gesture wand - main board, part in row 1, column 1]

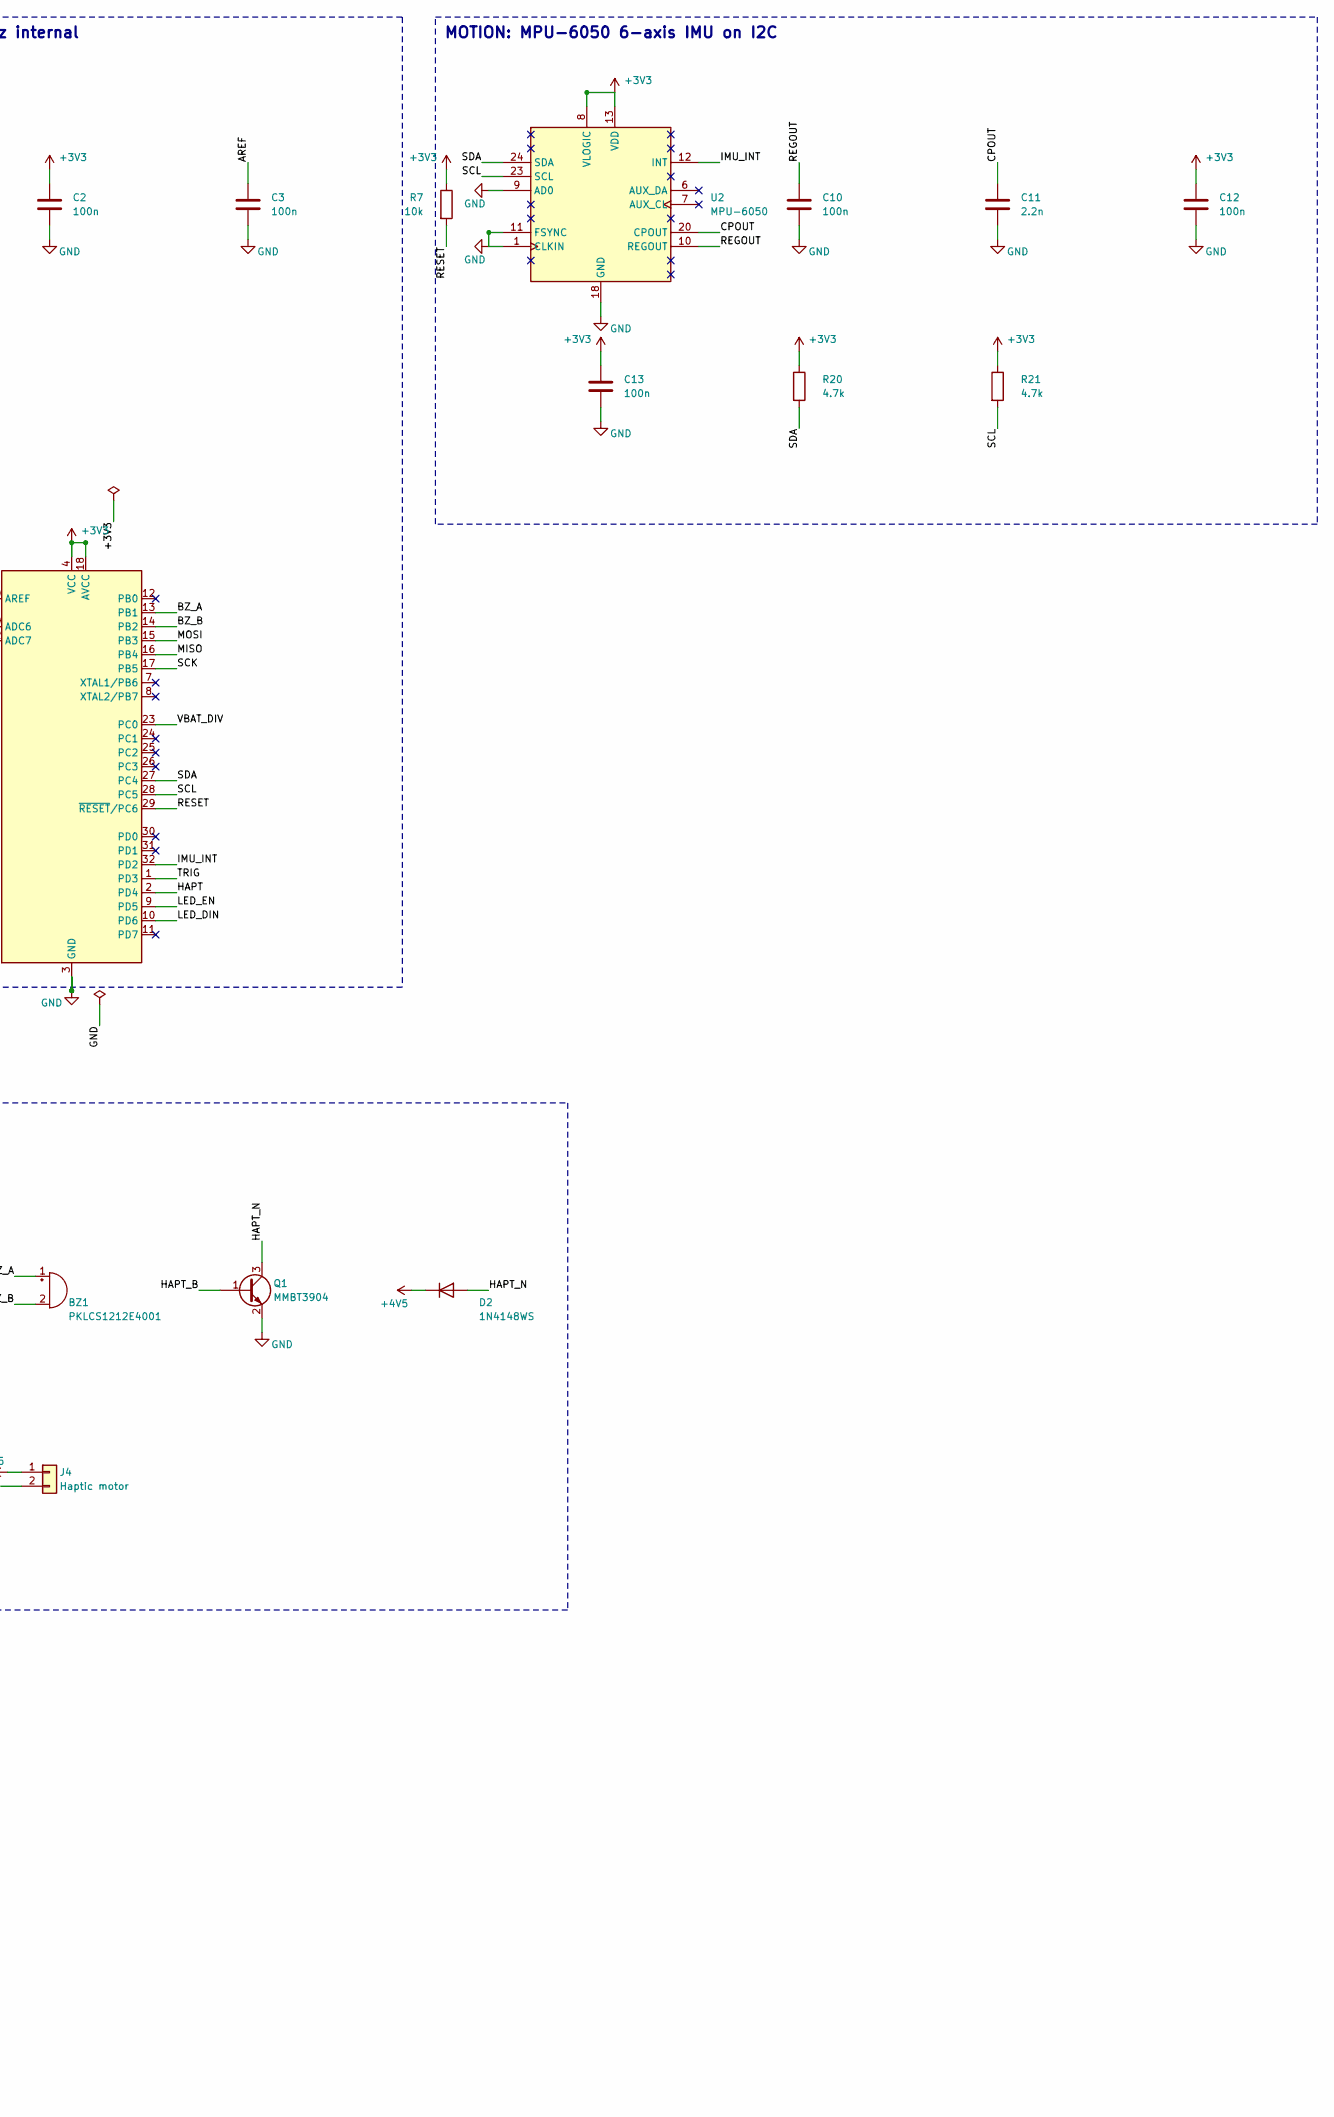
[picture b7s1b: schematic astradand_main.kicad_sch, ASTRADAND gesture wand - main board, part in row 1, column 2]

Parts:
BZ1: PKLCS1212E4001; Buzzer_Murata_PKLCS1212E
C1, C2, C3, C10, C12, C13, C20, C21, C22, C23, C24, C25: 100n; C_0603_1608Metric
C4, C7: 10u; C_0805_2012Metric
C5, C6: 1u; C_0603_1608Metric
C11: 2.2n; C_0603_1608Metric
D2: 1N4148WS; D_SOD-323
D11, D12, D13, D14, D15, D16: WS2812B-Mini; LED_WS2812B-Mini_PLCC4_3.5x3.5mm
D20: SS14; D_SMA
J1: BATT 3xAAA; JST_PH_B2B-PH-K_1x02_P2.00mm_Vertical
J2: ISP; PinHeader_2x03_P2.54mm_Vertical
J4: Haptic motor; JST_PH_B2B-PH-K_1x02_P2.00mm_Vertical
Q1, Q4: MMBT3904; SOT-23
Q2, Q3: AO3401A; SOT-23
R6, R34: 1k; R_0603_1608Metric
R7: 10k; R_0603_1608Metric
R20, R21: 4.7k; R_0603_1608Metric
R30: 330; R_0603_1608Metric
R31: 330k; R_0603_1608Metric
R32, R33: 100k; R_0603_1608Metric
SW1: Power; SW_SPDT_PCM12
SW2: Cast trigger; SW_SPST_B3U-1000P
TP1, TP2: TP; TestPoint_Pad_D1.5mm
U1: ATmega328P-AU; TQFP-32_7x7mm_P0.8mm
U2: MPU-6050; InvenSense_QFN-24_4x4mm_P0.5mm
U3: AP2112K-3.3; SOT-23-5

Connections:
+3V3: C1.1, C2.1, C6.1, C12.1, C13.1, J2.2, R7.1, R20.1, R21.1, U1.4 (VCC), U1.6 (VCC), U1.18 (AVCC), U2.8 (VLOGIC), U2.13 (VDD), U3.5 (VOUT)
+4V5: C4.1, C5.1, D2.1 (K), J4.1, Q2.2 (S), Q3.2 (S), R31.1, R33.1, TP1.1, U3.1 (VIN), U3.3 (EN)
AREF: C3.1, U1.20 (AREF)
BAT_P: J1.1, SW1.2 (B)
BAT_SW: Q2.3 (D), SW1.1 (A)
BZ_A: BZ1.1 (+), U1.13 (PB1)
BZ_B: BZ1.2 (-), U1.14 (PB2)
CPOUT: C11.1, U2.20 (CPOUT)
GND: C1.2, C2.2, C3.2, C4.2, C5.2, C6.2, C7.2, C10.2, C11.2, C12.2, C13.2, C20.2, C21.2, C22.2, C23.2, C24.2, C25.2, D11.3 (VSS), D12.3 (VSS), D13.3 (VSS), D14.3 (VSS), D15.3 (VSS), D16.3 (VSS), J1.2, J2.6, Q1.2 (E), Q2.1 (G), Q4.2 (E), R32.2, SW2.2, TP2.1, U1.3 (GND), U1.5 (GND), U1.21 (GND), U2.1 (CLKIN), U2.9 (AD0), U2.11 (FSYNC), U2.18 (GND), U3.2 (GND)
HAPT: R6.1, U1.2 (PD4)
HAPT_B: Q1.1 (B), R6.2
HAPT_N: D2.2 (A), J4.2, Q1.3 (C)
IMU_INT: U1.32 (PD2), U2.12 (INT)
LED_D1: D11.2 (DOUT), D12.4 (DIN)
LED_D2: D12.2 (DOUT), D13.4 (DIN)
LED_D3: D13.2 (DOUT), D14.4 (DIN)
LED_D4: D14.2 (DOUT), D15.4 (DIN)
LED_D5: D15.2 (DOUT), D16.4 (DIN)
LED_DIN: D11.4 (DIN), R30.1, R30.2, U1.10 (PD6)
LED_EN: R34.1, U1.9 (PD5)
LED_G: Q3.1 (G), Q4.3 (C), R33.2
LED_PB: Q4.1 (B), R34.2
LED_SRC: D20.2 (A), Q3.3 (D)
MISO: J2.1, U1.16 (PB4)
MOSI: J2.4, U1.15 (PB3)
REGOUT: C10.1, U2.10 (REGOUT)
RESET: J2.5, R7.2, U1.29 (~RESET/PC6)
SCK: J2.3, U1.17 (PB5)
SCL: R21.2, U1.28 (PC5), U2.23 (SCL)
SDA: R20.2, U1.27 (PC4), U2.24 (SDA)
TRIG: SW2.1, U1.1 (PD3)
VBAT_DIV: R31.2, R32.1, U1.23 (PC0)
VLED: C7.1, C20.1, C21.1, C22.1, C23.1, C24.1, C25.1, D11.1 (VDD), D12.1 (VDD), D13.1 (VDD), D14.1 (VDD), D15.1 (VDD), D16.1 (VDD), D20.1 (K)

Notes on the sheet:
POWER: 3xAAA, switch, reverse-polarity PMOS, 3.3 V LDO, LED supply diode, battery divider
MCU: ATmega328P-AU, 3.3 V, 8 MHz internal
MOTION: MPU-6050 6-axis IMU on I2C
LIGHT: six WS2812B-Mini pixels (daisy chain), each with 100 nF
TRIGGER, SOUND, HAPTIC
ASTRADAND: hold the trigger, draw a shape in the air, release. The 6-axis IMU is read over I2C at 50 Hz; the
ATmega matches the drawn path against six spell templates. Piezo is driven differentially from OC1A/OC1B
(D9/D10). LEDs are fed from +4V5 through a high-side switch (Q3, driven by Q4 from D5) and a Schottky (D20),
so the pixels draw nothing in sleep so that their 0.7 x VDD data threshold stays below the 3.3 V logic level;
the firmware caps the pixel current.

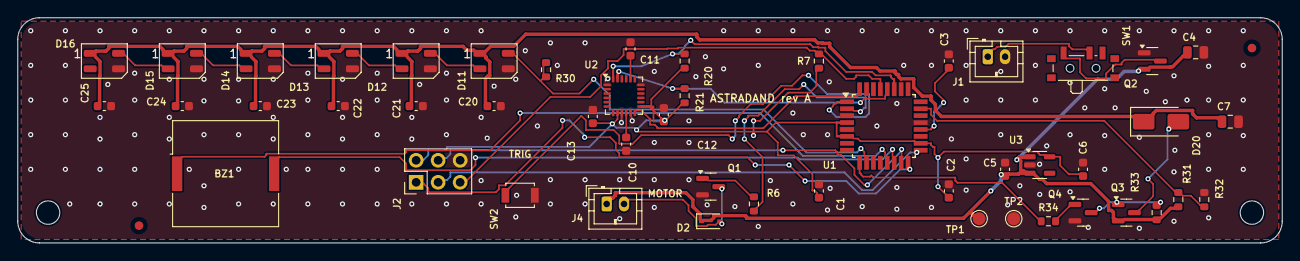
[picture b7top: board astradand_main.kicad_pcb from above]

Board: 2 copper layers, 146.0 x 26.0 mm, 53 parts (0 on the bottom side), 33 nets.

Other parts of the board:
FID1, FID2: Fiducial; Fiducial_1mm_Mask2mm
H1, H2: M2.5; MountingHole_2.7mm_M2.5
